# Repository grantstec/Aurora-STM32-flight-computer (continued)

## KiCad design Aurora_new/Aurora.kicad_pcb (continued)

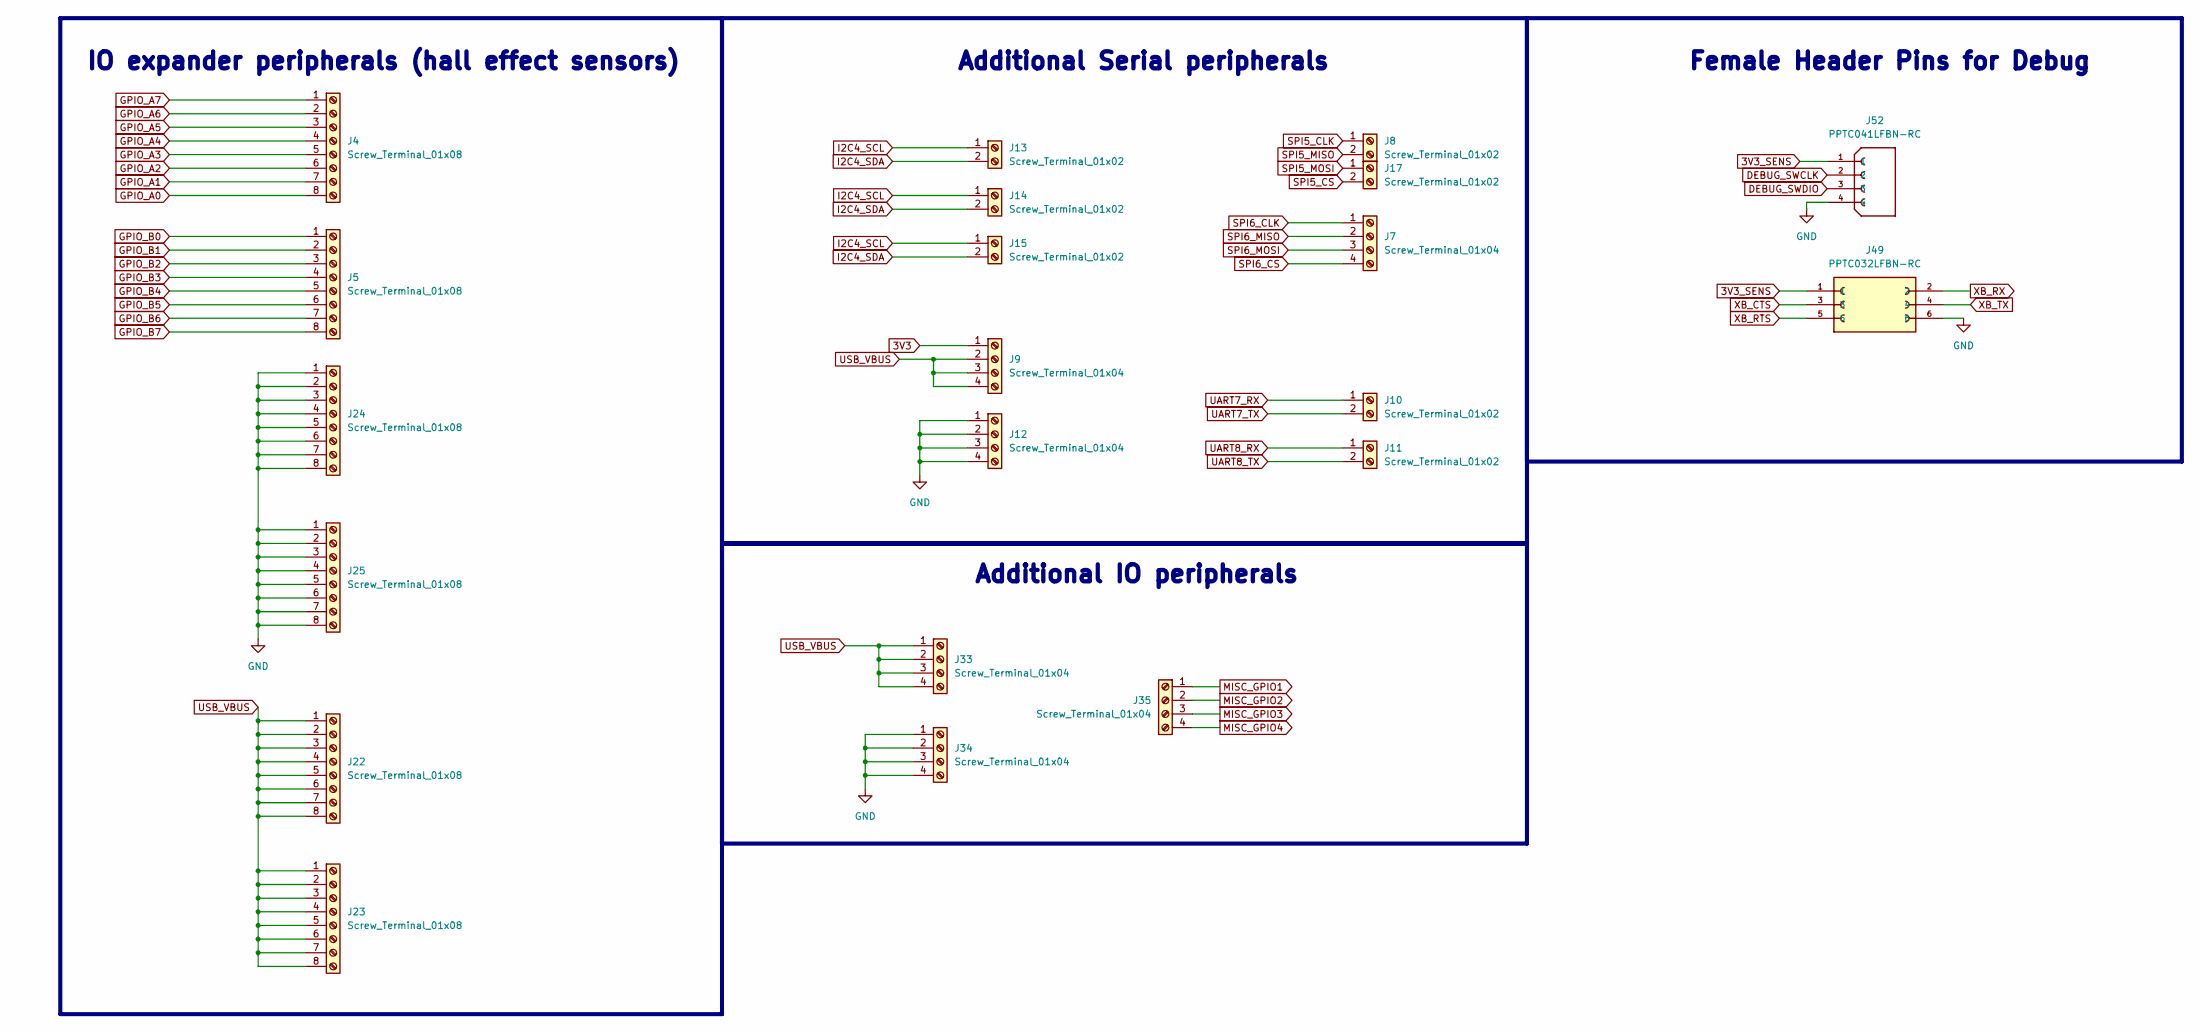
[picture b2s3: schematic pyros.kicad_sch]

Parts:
J4, J5, J22, J23, J24, J25: Screw_Terminal_01x08; PHOENIX_1725711
J7, J9, J12, J33, J34, J35: Screw_Terminal_01x04; PHOENIX_1725672
J8, J10, J11, J13, J14, J15, J17: Screw_Terminal_01x02; PHOENIX_1725656
J49: PPTC032LFBN-RC; PinSocket_2x03_P1.00mm_Vertical_SMD; PARTREV L
J52: PPTC041LFBN-RC; PinSocket_1x04_P2.54mm_Vertical; PARTREV J - 04/15/2015

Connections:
3V3: J9.1; also elsewhere on the board
3V3_SENS: J49.1, J52.1; also elsewhere on the board
DEBUG_SWCLK: J52.2; also elsewhere on the board
DEBUG_SWDIO: J52.3; also elsewhere on the board
GPIO_A0: J4.8; also elsewhere on the board
GPIO_A1: J4.7; also elsewhere on the board
GPIO_A2: J4.6; also elsewhere on the board
GPIO_A3: J4.5; also elsewhere on the board
GPIO_A4: J4.4; also elsewhere on the board
GPIO_A5: J4.3; also elsewhere on the board
GPIO_A6: J4.2; also elsewhere on the board
GPIO_A7: J4.1; also elsewhere on the board
GPIO_B0: J5.1; also elsewhere on the board
GPIO_B1: J5.2; also elsewhere on the board
GPIO_B2: J5.3; also elsewhere on the board
GPIO_B3: J5.4; also elsewhere on the board
GPIO_B4: J5.5; also elsewhere on the board
GPIO_B5: J5.6; also elsewhere on the board
GPIO_B6: J5.7; also elsewhere on the board
GPIO_B7: J5.8; also elsewhere on the board
I2C4_SCL: J13.1, J14.1, J15.1; also elsewhere on the board
I2C4_SDA: J13.2, J14.2, J15.2; also elsewhere on the board
MISC_GPIO1: J35.1; also elsewhere on the board
MISC_GPIO2: J35.2; also elsewhere on the board
MISC_GPIO3: J35.3; also elsewhere on the board
MISC_GPIO4: J35.4; also elsewhere on the board
SPI6_CLK: J7.1; also elsewhere on the board
SPI6_CS: J7.4; also elsewhere on the board
SPI6_MISO: J7.2; also elsewhere on the board
SPI6_MOSI: J7.3; also elsewhere on the board
UART7_RX: J10.1; also elsewhere on the board
UART7_TX: J10.2; also elsewhere on the board
UART8_RX: J11.1; also elsewhere on the board
UART8_TX: J11.2; also elsewhere on the board
USB_VBUS: J9.2, J9.3, J9.4, J22.1, J22.2, J22.3, J22.4, J22.5, J22.6, J22.7, J22.8, J23.1, J23.2, J23.3, J23.4, J23.5, J23.6, J23.7, J23.8, J33.1, J33.2, J33.3, J33.4; also elsewhere on the board
VDDSMPS: J12.1, J12.2, J12.3, J12.4, J24.1, J24.2, J24.3, J24.4, J24.5, J24.6, J24.7, J24.8, J25.1, J25.2, J25.3, J25.4, J25.5, J25.6, J25.7, J25.8, J34.1, J34.2, J34.3, J34.4, J49.6, J52.4; also elsewhere on the board
XB_CTS: J49.3; also elsewhere on the board
XB_RTS: J49.5; also elsewhere on the board
XB_RX: J49.2; also elsewhere on the board
XB_TX: J49.4; also elsewhere on the board

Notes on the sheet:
Additional IO peripherals
Additional Serial peripherals
IO expander peripherals (hall effect sensors)
Female Header Pins for Debug

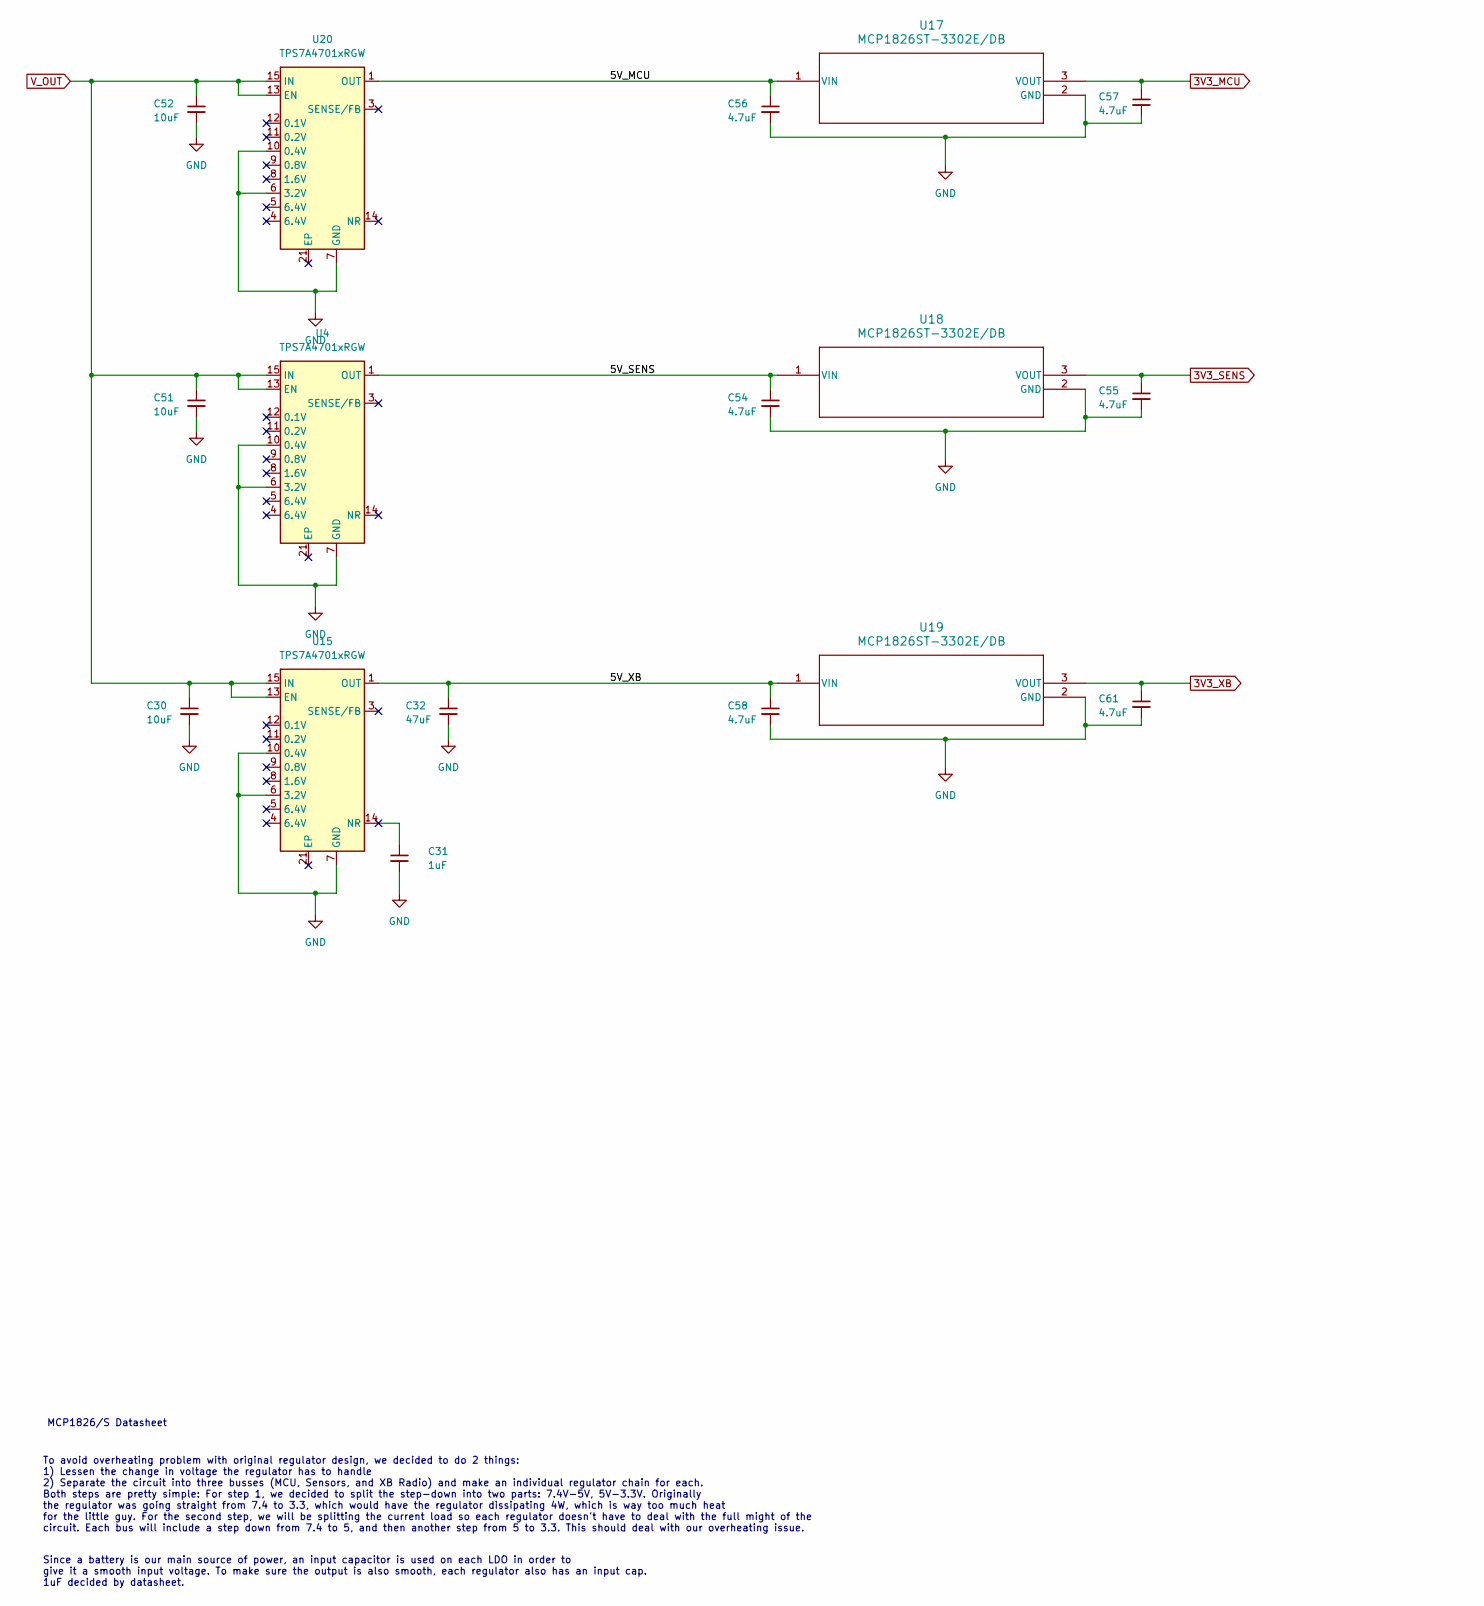
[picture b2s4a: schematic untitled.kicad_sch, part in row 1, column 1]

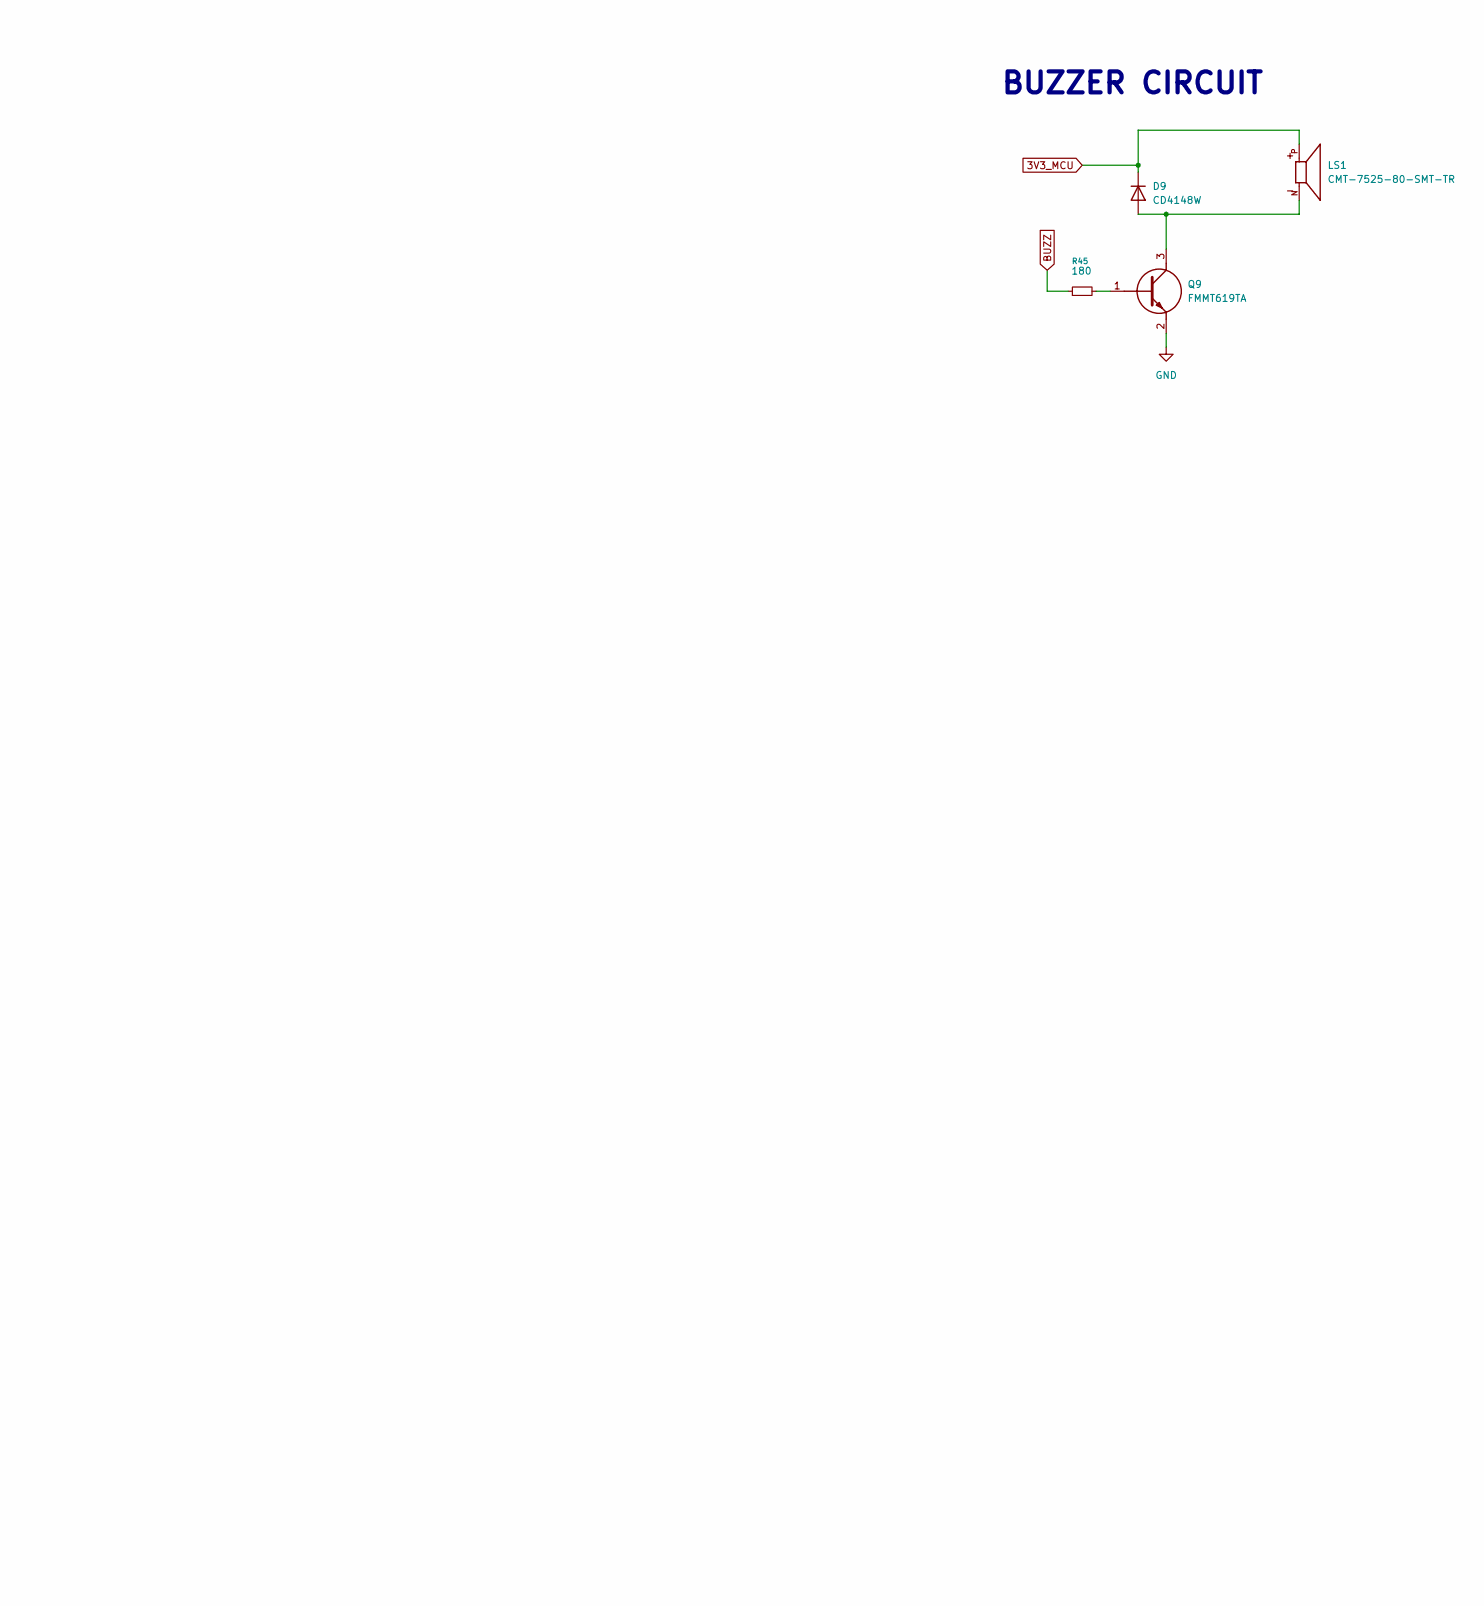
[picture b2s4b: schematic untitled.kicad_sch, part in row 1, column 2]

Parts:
C30, C51, C52: 10uF; C_0805_2012Metric
C31: 1uF; C_0805_2012Metric
C32: 47uF; C_0805_2012Metric
C54, C55, C56, C57, C58, C61: 4.7uF; C_0805_2012Metric
D9: CD4148W; D_0805_2012Metric
LS1: CMT-7525-80-SMT-TR; XDCR_CMT-7525-80-SMT-TR; PARTREV N/A
Q9: FMMT619TA; SOT95P237X112-3N; Mouser Part Number 522-FMMT619TA
R45: 180; R_0805_2012Metric
U4, U15, U20: TPS7A4701xRGW; Texas_RGW0020A_VQFN-20-1EP_5x5mm_P0.65mm_EP3.15x3.15mm
U17, U18, U19: MCP1826ST-3302E/DB; SOT-223_3MC_MCH-L

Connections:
3V3_MCU: C57.1, D9.1 (K), LS1.P, U17.3 (VOUT); also elsewhere on the board
3V3_SENS: C55.1, U18.3 (VOUT); also elsewhere on the board
3V3_XB: C61.1, U19.3 (VOUT); also elsewhere on the board
/Chips/Regulators/5V_MCU: C56.1, U17.1 (VIN), U20.1 (OUT), U20.20 (OUT)
/Chips/Regulators/5V_SENS: C54.1, U4.1 (OUT), U4.20 (OUT), U18.1 (VIN)
/Chips/Regulators/5V_XB: C32.1, C58.1, U15.1 (OUT), U15.20 (OUT), U19.1 (VIN)
BUZZ: R45.1; also elsewhere on the board
unnamed: D9.2 (A), LS1.N, Q9.3 (C)
unnamed: Q9.1 (B), R45.2
VDDSMPS: C30.2, C31.2, C32.2, C51.2, C52.2, C54.2, C55.2, C56.2, C57.2, C58.2, C61.2, Q9.2 (E), U4.6 (3.2V), U4.7 (GND), U4.10 (0.4V), U15.6 (3.2V), U15.7 (GND), U15.10 (0.4V), U17.2 (GND), U18.2 (GND), U19.2 (GND), U20.6 (3.2V), U20.7 (GND), U20.10 (0.4V); also elsewhere on the board
V_OUT: C30.1, C51.1, C52.1, U4.13 (EN), U4.15 (IN), U4.16 (IN), U15.13 (EN), U15.15 (IN), U15.16 (IN), U20.13 (EN), U20.15 (IN), U20.16 (IN); also elsewhere on the board

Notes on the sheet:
MCP1826/S Datasheet
BUZZER CIRCUIT
To avoid overheating problem with original regulator design, we decided to do 2 things: 1) Lessen the change in voltage the regulator has to handle 2) Separate the circuit into three busses (MCU, Sensors, and XB Radio) and make an individual regulator chain for each. Both steps are pretty simple: F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
Since a battery is our main source of power, an input capacitor is used on each LDO in order to give it a smooth input voltage. To make sure the output is also smooth, each regulator also has an input cap. 1uF decided by datasheet.

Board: 2 copper layers, 129 parts (0 on the bottom side), 133 nets, no tracks yet.

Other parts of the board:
J2: Screw_Terminal_01x04; PHOENIX_1984633

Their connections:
SPI5_CLK: J2.1; also elsewhere on the board
SPI5_CS: J2.4; also elsewhere on the board
SPI5_MISO: J2.2; also elsewhere on the board
SPI5_MOSI: J2.3; also elsewhere on the board

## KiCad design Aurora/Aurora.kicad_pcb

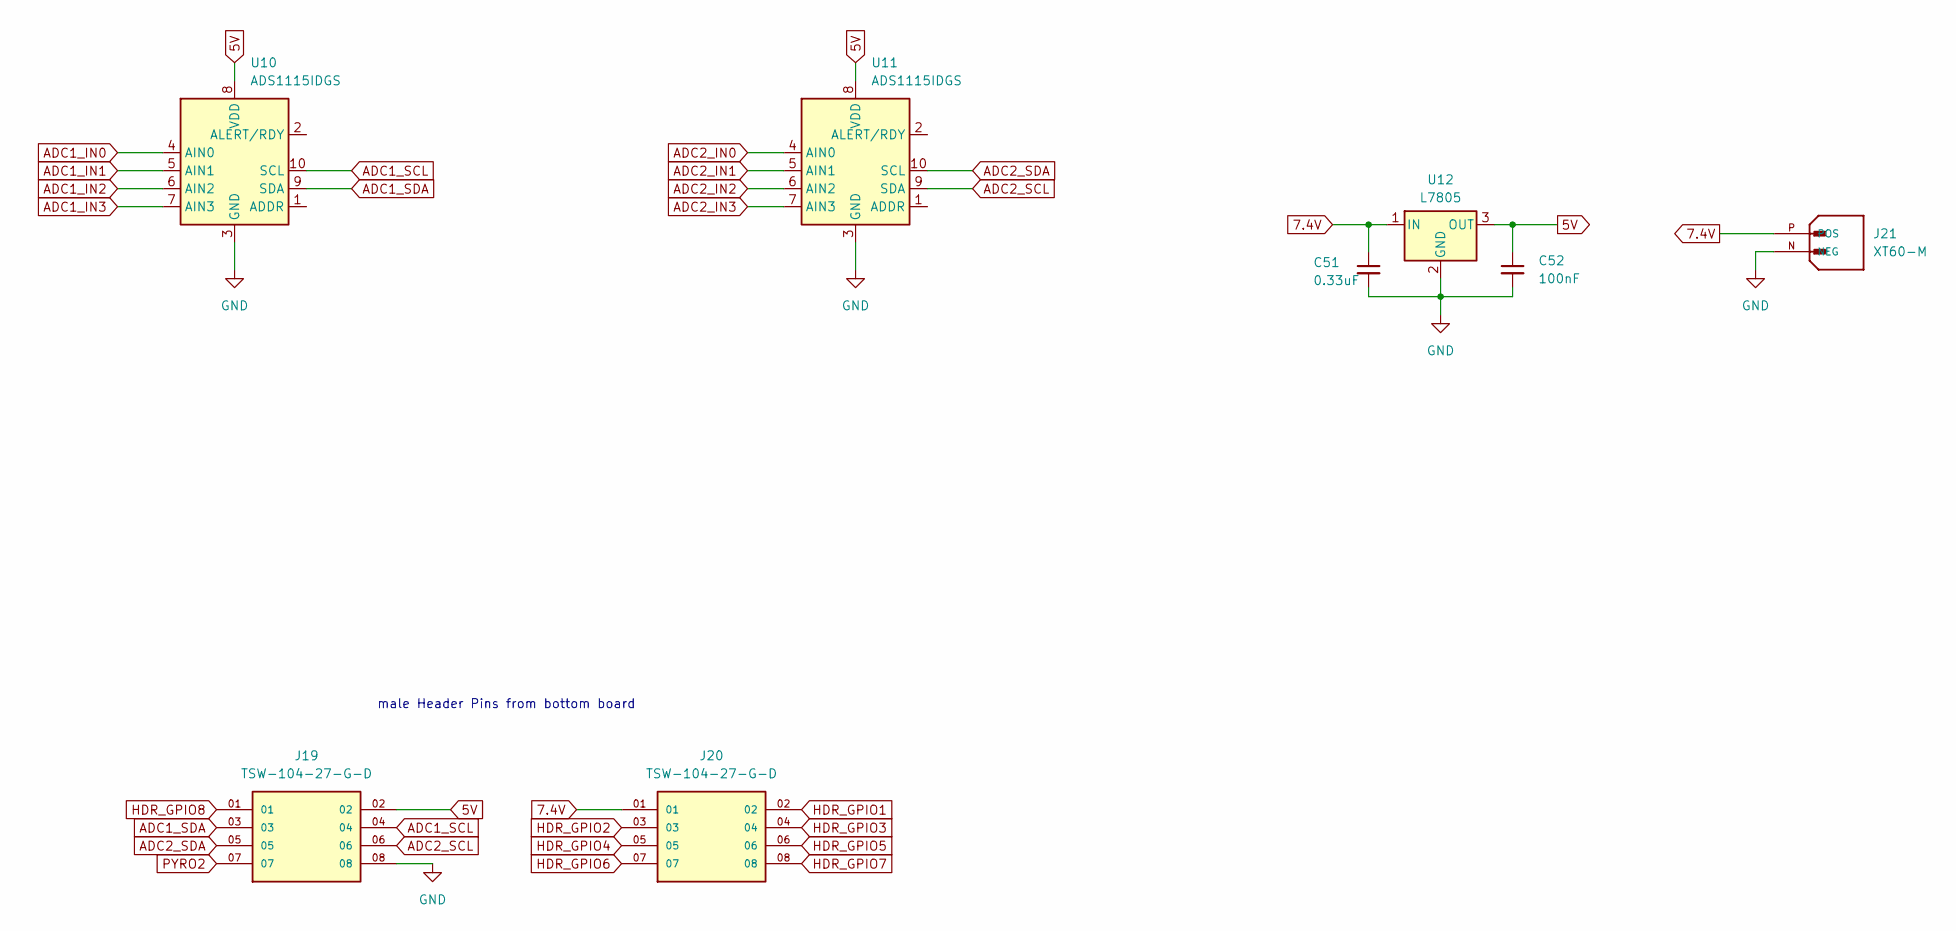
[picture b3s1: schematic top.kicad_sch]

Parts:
C51: 0.33uF; C_1206_3216Metric
C52: 100nF; C_1206_3216Metric
J19, J20: TSW-104-27-G-D; SAMTEC_TSW-104-27-G-D; PARTREV R
J21: XT60-M; AMASS_XT60-M; PARTREV V1.2
U10, U11: ADS1115IDGS; TSSOP-10_3x3mm_P0.5mm
U12: L7805; TO255P1020X450X2000-3

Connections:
5V: C52.1, J19.02, U10.8 (VDD), U11.8 (VDD), U12.3 (OUT); also elsewhere on the board
7.4V: C51.1, J20.01, J21.P (POS), U12.1 (IN); also elsewhere on the board
ADC1_IN0: U10.4 (AIN0); also elsewhere on the board
ADC1_IN1: U10.5 (AIN1); also elsewhere on the board
ADC1_IN2: U10.6 (AIN2); also elsewhere on the board
ADC1_IN3: U10.7 (AIN3); also elsewhere on the board
ADC1_SCL: J19.04, U10.10 (SCL); also elsewhere on the board
ADC1_SDA: J19.03, U10.9 (SDA); also elsewhere on the board
ADC2_IN0: U11.4 (AIN0); also elsewhere on the board
ADC2_IN1: U11.5 (AIN1); also elsewhere on the board
ADC2_IN2: U11.6 (AIN2); also elsewhere on the board
ADC2_IN3: U11.7 (AIN3); also elsewhere on the board
ADC2_SCL: J19.06, U11.9 (SDA); also elsewhere on the board
ADC2_SDA: J19.05, U11.10 (SCL); also elsewhere on the board
GND: C51.2, C52.2, J19.08, J21.N (NEG), U10.3 (GND), U11.3 (GND), U12.2 (GND); also elsewhere on the board
HDR_GPIO1: J20.02; also elsewhere on the board
HDR_GPIO2: J20.03; also elsewhere on the board
HDR_GPIO3: J20.04; also elsewhere on the board
HDR_GPIO4: J20.05; also elsewhere on the board
HDR_GPIO5: J20.06; also elsewhere on the board
HDR_GPIO6: J20.07; also elsewhere on the board
HDR_GPIO7: J20.08; also elsewhere on the board
HDR_GPIO8: J19.01; also elsewhere on the board
PYRO2: J19.07; also elsewhere on the board

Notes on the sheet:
male Header Pins from bottom board
